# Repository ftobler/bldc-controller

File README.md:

# A bunch of BLDC controller and related PCB

Software for STM32.

PCB in Eagle.

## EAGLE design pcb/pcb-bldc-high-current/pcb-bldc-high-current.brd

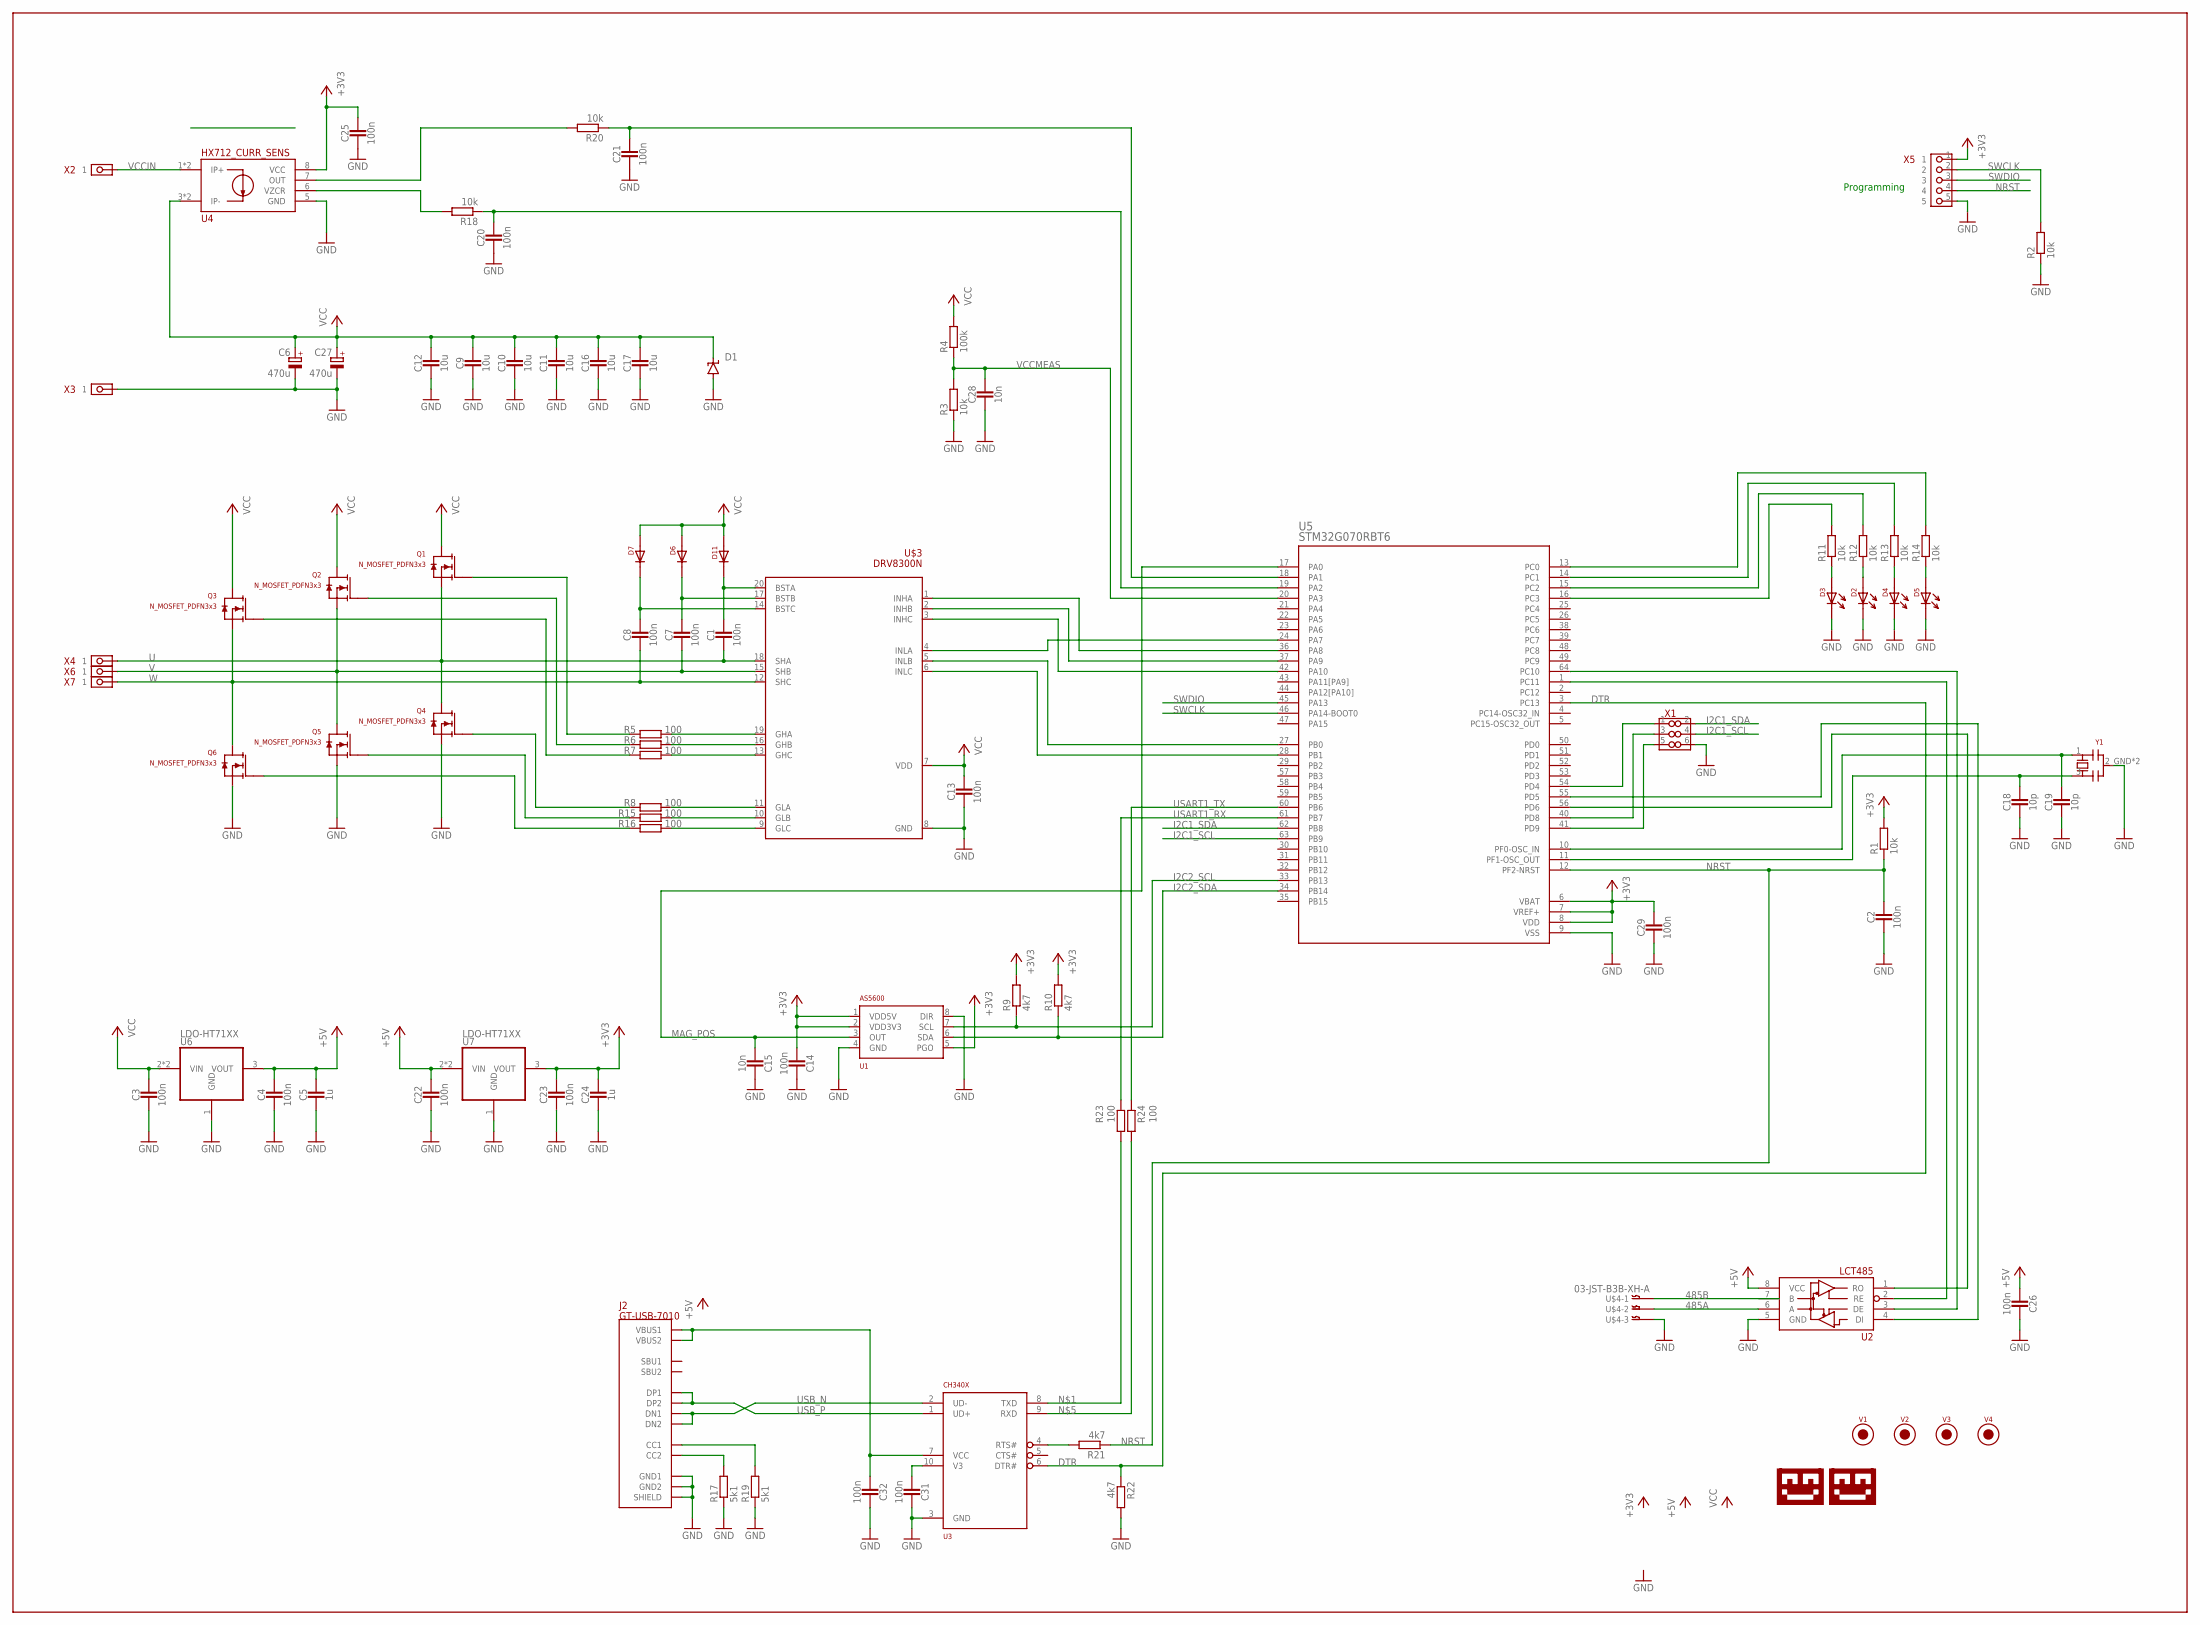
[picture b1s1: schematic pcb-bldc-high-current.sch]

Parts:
C1, C2, C3, C4, C7, C8, C13, C14, C20, C21, C22, C23, C25, C26, C29, C31, C32: 100n; 0603_CAP
C5, C24: 1u; 0603_CAP
C6, C27: 470u; 153CLV-1010
C9, C10, C11, C12, C16, C17: 10u; 1206_CAP
C15, C28: 10n; 0603_CAP
C18, C19: 10p; 0603_CAP
D1: SUPPRESSOR-SMBJ; SMBJ
D2, D3, D4, D5: LED-0805; 0805-DOT
D6, D7, D11: DIODESOD123; SOD123
J2: GT-USB-7010
Q1, Q2, Q3, Q4, Q5, Q6: N_MOSFET_PDFN3x3; DFN3X3-8L
R1, R2, R3, R11, R12, R13, R14, R18, R20: 10k; 0603-RES
R4: 100k; 0603-RES
R5, R6, R7, R8, R15, R16, R23, R24: 100; 0603-RES
R9, R10, R21, R22: 4k7; 0603-RES
R17, R19: 5k1; 0603-RES
U1: AS5600; SOIC-8
U2: LCT485_BUS_TRANSCEIVER; SOIC-8
U3: CH340X; MSOP-10
U4: HX712_CURR_SENS; SOIC-8
U5: STM32G070RBT6; LQFP-64
U6, U7: LDO-HT71XX; SOT-89
U$1: LOGO-TOBENG-1MM-FINISH; TOBENG-1MM-FINISH
U$2: LOGO-0.25MM
U$3: DRV8300N; TSSOP20
U$4: 03-JST-B3B-XH-A; B3B-XH
V1, V2, V3, V4: FIDUCIAL2MM; FIDUCIAL_2MM
X1: PIN_3X2HD; PIN_3X2_HD
X2, X3: PIN_1X1WELDINGTERMINAL; XFCNTS34031
X4, X6, X7: PIN_1X1WIRE1; PIN_1X1_SOLDERWIRE_1
X5: PIN_5X1HD; PIN_5X1_HD
Y1: 3213-QUARZ3225; 3225-QUARZ

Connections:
485A: U2.6 (A), U$4.P$2
485B: U2.7 (B), U$4.P$1
+3V3: C14.1, C23.1, C24.1, C25.1, C29.1, R1.2, R9.2, R10.2, U1.1 (VDD5V), U1.2 (VDD3V3), U1.5 (PGO), U4.8 (VCC), U5.6 (VBAT), U5.7 (VREF+), U5.8 (VDD), U7.3 (VOUT), X5.1
+5V: C4.1, C5.1, C22.1, C26.1, U2.8 (VCC), U6.3 (VOUT), U7.2 (VIN), U7.2@1 (VIN)
DTR: R22.1, U3.6 (DTR#), U5.3 (PC13)
GND: C2.2, C3.2, C4.2, C5.2, C6.-, C9.2, C10.2, C11.2, C12.2, C13.2, C14.2, C15.2, C16.2, C17.2, C18.2, C19.2, C20.2, C21.2, C22.2, C23.2, C24.2, C25.2, C26.2, C27.-, C28.2, C29.2, C31.2, C32.2, D1.A, D2.2, D3.2, D4.2, D5.2, J2.13 (SHIELD), J2.14 (SHIELD), J2.15 (SHIELD), J2.16 (SHIELD), J2.A1B12 (GND1), J2.B1A12 (GND2), J2.PAD1 (SHIELD), J2.PAD2 (SHIELD), J2.PAD3 (SHIELD), J2.PAD4 (SHIELD), J2.PAD5 (SHIELD), J2.PAD6 (SHIELD), Q4.S1 (S), Q4.S2 (S), Q4.S3 (S), Q5.S1 (S), Q5.S2 (S), Q5.S3 (S), Q6.S1 (S), Q6.S2 (S), Q6.S3 (S), R2.1, R3.1, R17.1, R19.1, R22.2, U1.4 (GND), U1.8 (DIR), U2.5 (GND), U3.3 (GND), U4.5 (GND), U5.9 (VSS), U6.1 (GND), U7.1 (GND), U$3.8 (GND), U$4.P$3, X1.6, X3.1, X3.2, X3.3, X3.4, X5.5, Y1.2_GND (2), Y1.4_GND (2)
I2C1_SCL: U5.63 (PB9), X1.4
I2C1_SDA: U5.62 (PB8), X1.2
I2C2_SCL: R9.1, U1.7 (SCL), U5.33 (PB13)
I2C2_SDA: R10.1, U1.6 (SDA), U5.34 (PB14)
MAG_POS: C15.1, U1.3 (OUT), U5.17 (PA0)
unnamed: R23.2, U3.8 (TXD)
unnamed: C18.1, U5.11 (PF1-OSC_OUT), Y1.3
unnamed: C19.1, U5.10 (PF0-OSC_IN), Y1.1
unnamed: C1.1, D11.C (2), U$3.20 (BSTA)
unnamed: R24.2, U3.9 (RXD)
unnamed: C7.1, D6.C (2), U$3.17 (BSTB)
unnamed: C8.1, D7.C (2), U$3.14 (BSTC)
unnamed: D3.1, R11.1
unnamed: U5.41 (PD9), X1.5
unnamed: Q4.G, R8.2
unnamed: Q5.G, R15.2
unnamed: Q6.G, R16.2
unnamed: Q1.G, R5.2
unnamed: Q2.G, R6.2
unnamed: Q3.G, R7.2
unnamed: D2.1, R12.1
unnamed: D4.1, R13.1
unnamed: D5.1, R14.1
unnamed: R14.2, U5.13 (PC0)
unnamed: R13.2, U5.14 (PC1)
unnamed: R12.2, U5.15 (PC2)
unnamed: R11.2, U5.16 (PC3)
unnamed: U5.36 (PA8), U$3.1 (INHA)
unnamed: U5.24 (PA7), U$3.4 (INLA)
unnamed: U5.37 (PA9), U$3.2 (INHB)
unnamed: U5.27 (PB0), U$3.5 (INLB)
unnamed: U5.42 (PA10), U$3.3 (INHC)
unnamed: U5.28 (PB1), U$3.6 (INLC)
unnamed: R5.1, U$3.19 (GHA)
unnamed: R6.1, U$3.16 (GHB)
unnamed: R7.1, U$3.13 (GHC)
unnamed: R8.1, U$3.11 (GLA)
unnamed: R15.1, U$3.10 (GLB)
unnamed: R16.1, U$3.9 (GLC)
unnamed: C32.1, J2.A4B9 (VBUS1), J2.B4A9 (VBUS2), U3.7 (VCC)
unnamed: R21.2, U3.4 (RTS#)
unnamed: U5.40 (PD8), X1.3
unnamed: C20.1, R18.1, U5.19 (PA2)
unnamed: C21.1, R20.1, U5.18 (PA1)
unnamed: R18.2, U4.6 (VZCR)
unnamed: R20.2, U4.7 (OUT)
unnamed: U2.1 (RO), U5.56 (PD6)
unnamed: U2.2 (RE), U5.1 (PC11)
unnamed: U2.3 (DE), U5.64 (PC10)
unnamed: U2.4 (DI), U5.55 (PD5)
unnamed: U5.54 (PD4), X1.1
unnamed: J2.B5 (CC2), R17.2
unnamed: J2.A5 (CC1), R19.2
unnamed: C31.1, U3.10 (V3)
NRST: C2.1, R1.1, R21.1, U5.12 (PF2-NRST), X5.4
SWCLK: R2.2, U5.46 (PA14-BOOT0), X5.2
SWDIO: U5.45 (PA13), X5.3
U: C1.2, Q1.S1 (S), Q1.S2 (S), Q1.S3 (S), Q4.D, U$3.18 (SHA), X4.P$1, X4.P$2, X4.P$3, X4.P$4, X4.P$5, X4.P$6, X4.P$7, X4.P$8, X4.P$9, X4.P$10, X4.P$11, X4.P$12, X4.P$13, X4.P$14, X4.P$15, X4.P$16, X4.P$17, X4.P$18, X4.P$19, X4.P$20
USART1_RX: R23.1, U5.61 (PB7)
USART1_TX: R24.1, U5.60 (PB6)
USB_N: J2.A7 (DN1), J2.B7 (DN2), U3.2 (UD-)
USB_P: J2.A6 (DP1), J2.B6 (DP2), U3.1 (UD+)
V: C7.2, Q2.S1 (S), Q2.S2 (S), Q2.S3 (S), Q5.D, U$3.15 (SHB), X6.P$1, X6.P$2, X6.P$3, X6.P$4, X6.P$5, X6.P$6, X6.P$7, X6.P$8, X6.P$9, X6.P$10, X6.P$11, X6.P$12, X6.P$13, X6.P$14, X6.P$15, X6.P$16, X6.P$17, X6.P$18, X6.P$19, X6.P$20
VCC: C3.1, C6.+, C9.1, C10.1, C11.1, C12.1, C13.1, C16.1, C17.1, C27.+, D1.C, D6.A (1), D7.A (1), D11.A (1), Q1.D, Q2.D, Q3.D, R4.2, U4.3 (IP-), U4.4 (IP-), U6.2 (VIN), U6.2@1 (VIN), U$3.7 (VDD)
VCCIN: U4.1 (IP+), U4.2 (IP+), X2.1, X2.2, X2.3, X2.4
VCCMEAS: C28.1, R3.2, R4.1, U5.20 (PA3)
W: C8.2, Q3.S1 (S), Q3.S2 (S), Q3.S3 (S), Q6.D, U$3.12 (SHC), X7.P$1, X7.P$2, X7.P$3, X7.P$4, X7.P$5, X7.P$6, X7.P$7, X7.P$8, X7.P$9, X7.P$10, X7.P$11, X7.P$12, X7.P$13, X7.P$14, X7.P$15, X7.P$16, X7.P$17, X7.P$18, X7.P$19, X7.P$20

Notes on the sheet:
Programming

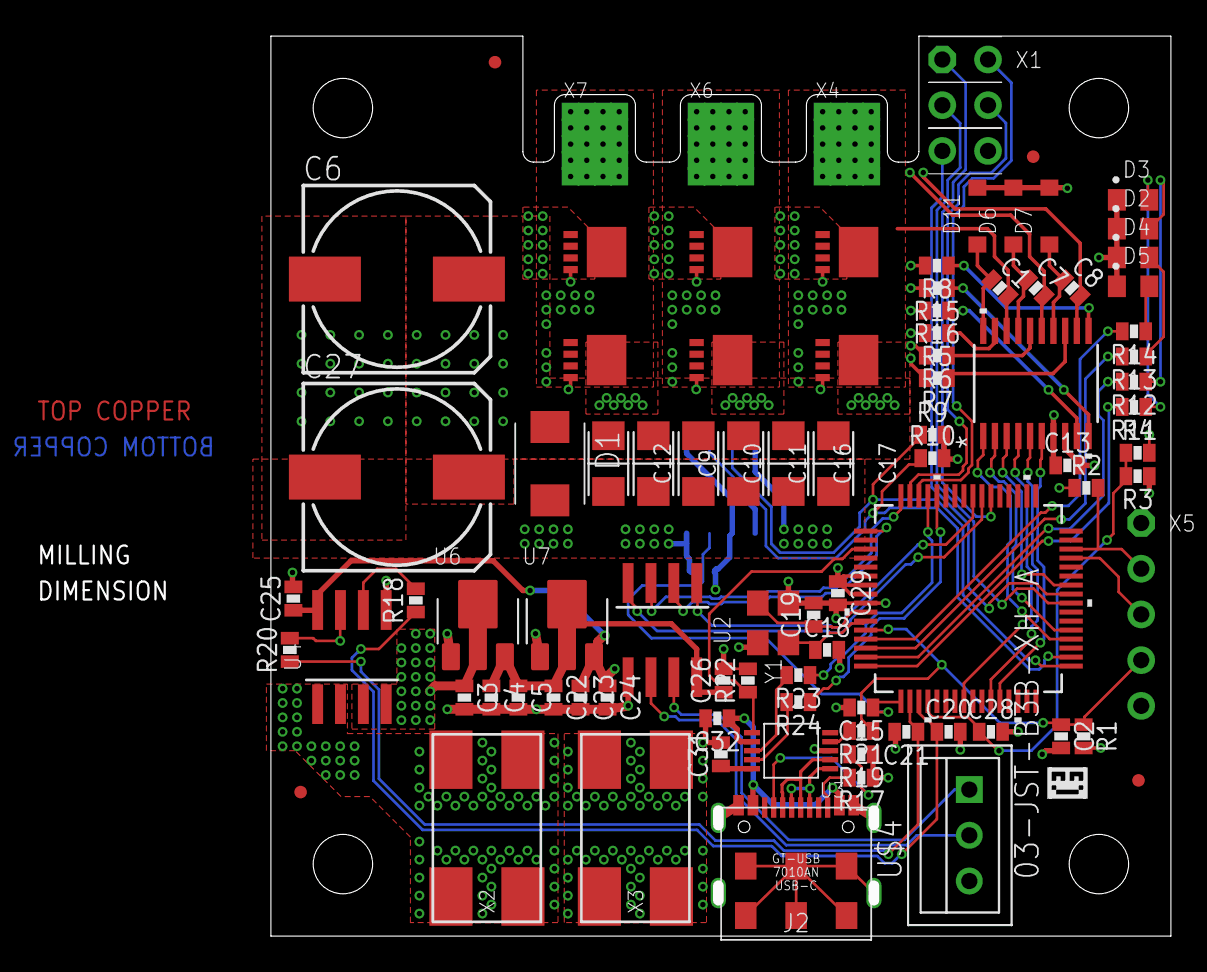
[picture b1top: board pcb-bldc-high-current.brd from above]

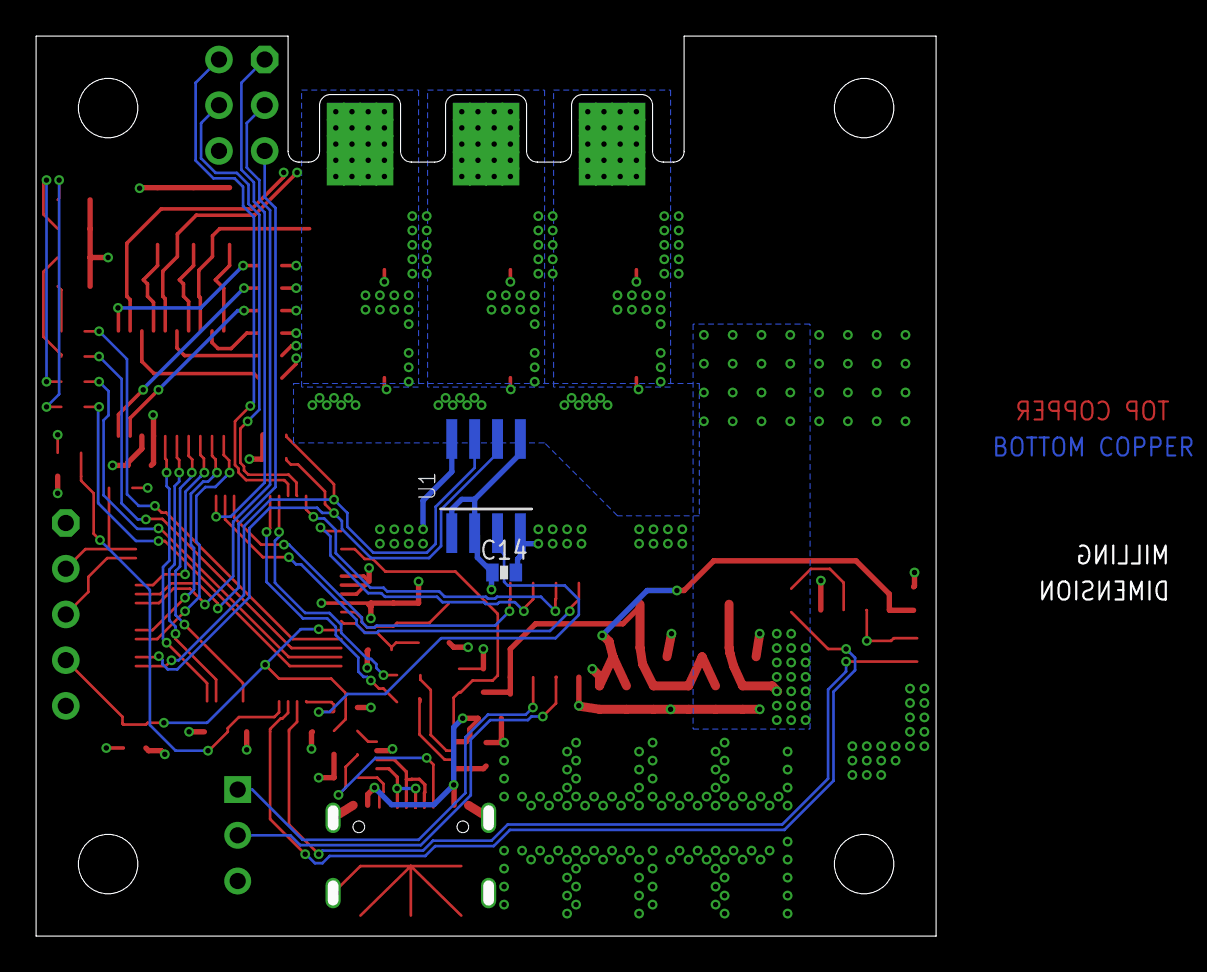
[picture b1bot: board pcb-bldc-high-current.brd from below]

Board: 4 copper layers, 50.0 x 50.0 mm, 93 parts (3 on the bottom side), 73 nets.

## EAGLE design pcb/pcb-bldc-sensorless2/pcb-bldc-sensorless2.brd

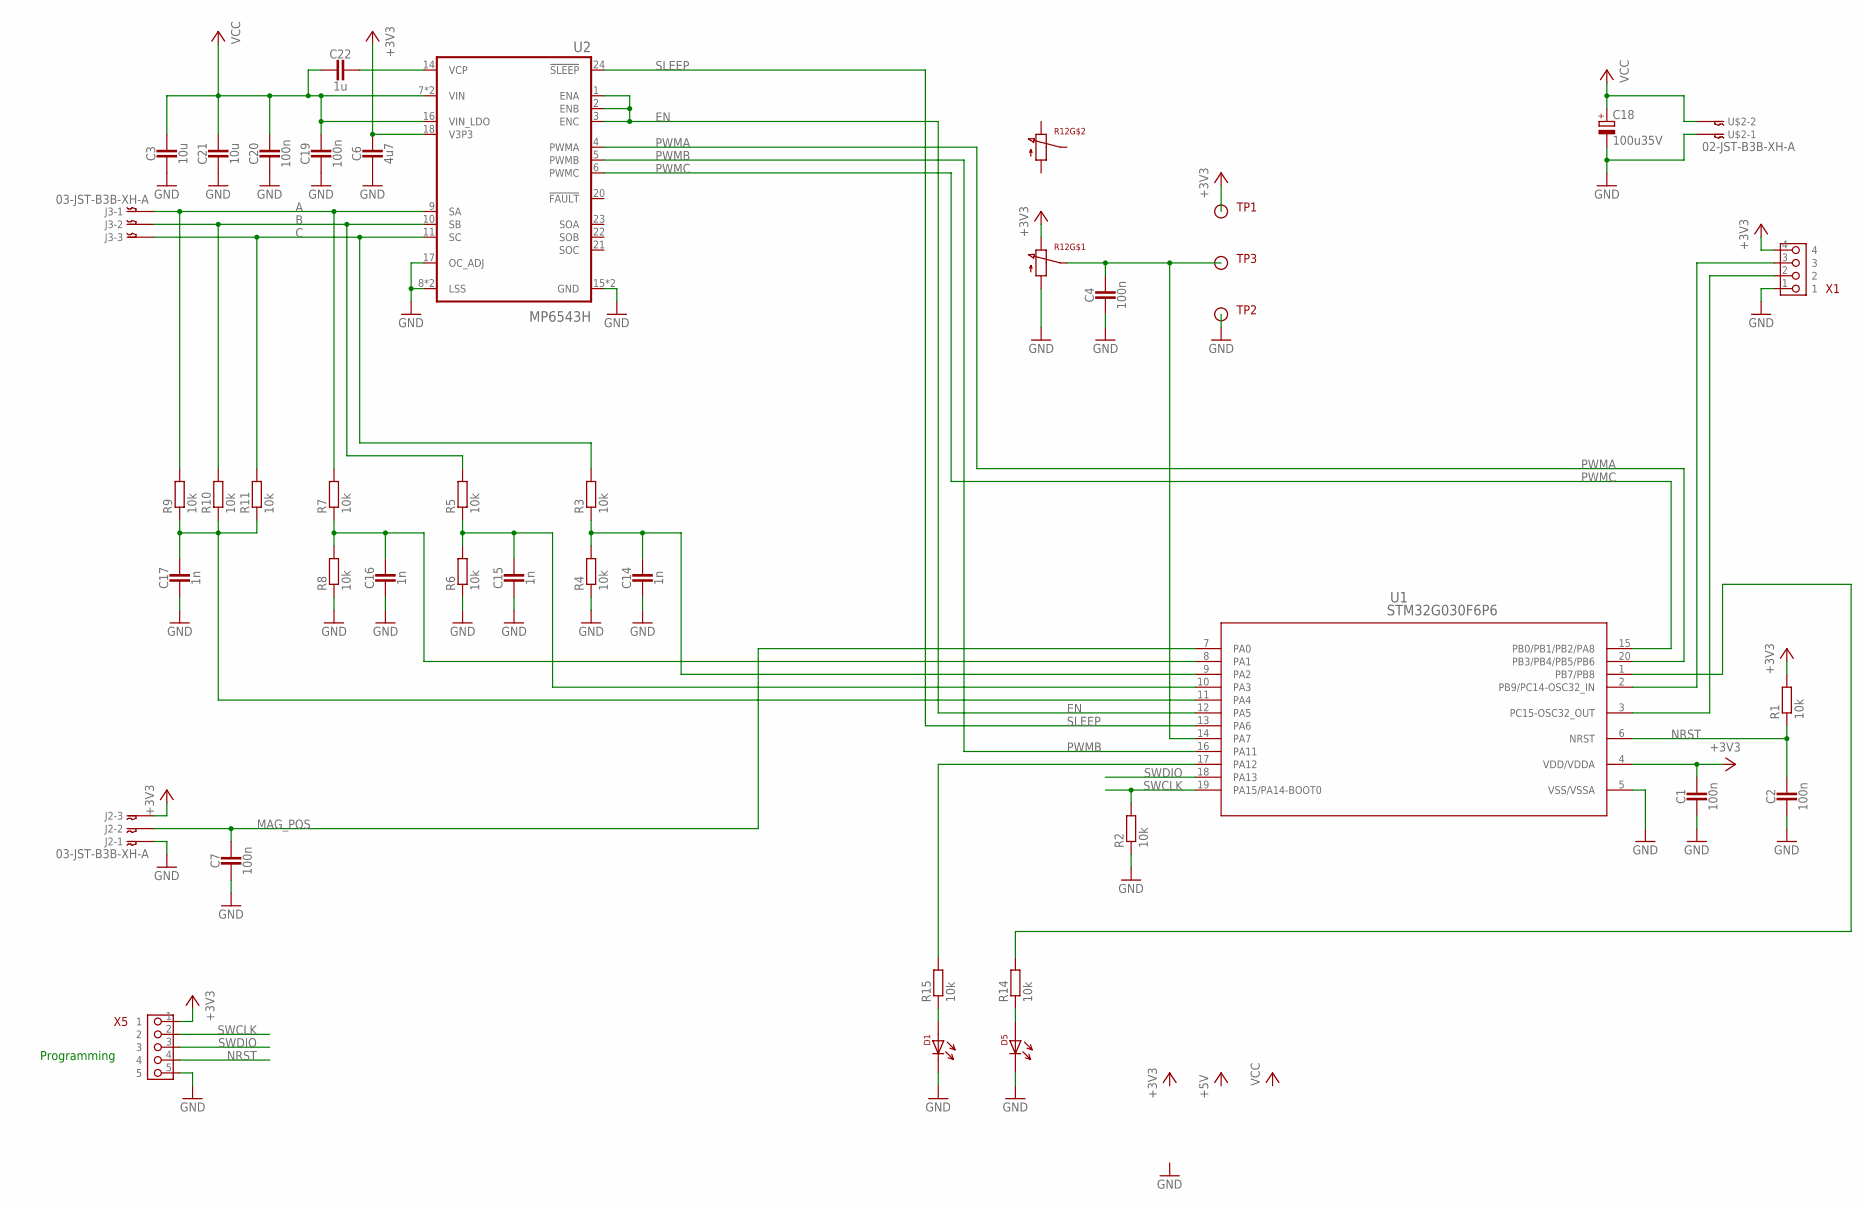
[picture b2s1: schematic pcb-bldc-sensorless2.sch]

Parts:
C1, C2, C4, C7, C19, C20: 100n; 0603_CAP
C3, C21: 10u; 1206_CAP
C6: 4u7; 0805_CAP
C14, C15, C16, C17: 1n; 0603_CAP
C18: 100u35V; 153CLV-0605
C22: 1u; 0603_CAP
D1, D5: LED-0805; 0805-DOT
J2, J3: 03-JST-B3B-XH-A; B3B-XH
R1, R2, R3, R4, R5, R6, R7, R8, R9, R10, R11, R14, R15: 10k; 0603-RES
R12: POTDUAL; ALPS_RK097
TP1, TP2, TP3: TESTPIN; PIN-SMD-1X1-TEST_1M5
U1: STM32G030F6P6; TSSOP20
U2: MP6543H; QFN24
U$2: 02-JST-B3B-XH-A; B2B-XH
X1: PIN_4X1HD; PIN_4X1_HD
X5: PIN_5X1HD; PIN_5X1_HD

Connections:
+3V3: C1.1, C6.P$1 (1), J2.P$3, R1.2, R12.R11 (1), TP1.1, U1.4 (VDD/VDDA), U2.18 (V3P3), X1.4, X5.1
A: J3.P$1, R7.2, R9.2, U2.9 (SA)
B: J3.P$2, R5.2, R10.2, U2.10 (SB)
C: J3.P$3, R3.2, R11.2, U2.11 (SC)
EN: U1.12 (PA5), U2.1 (ENA), U2.2 (ENB), U2.3 (ENC)
GND: C1.2, C2.2, C3.2, C4.2, C6.P$2 (2), C7.2, C14.2, C15.2, C16.2, C17.2, C18.-, C19.2, C20.2, C21.2, D1.2, D5.2, J2.P$1, R2.1, R4.1, R6.1, R8.1, R12.R13 (3), TP2.1, U1.5 (VSS/VSSA), U2.8 (LSS), U2.12 (LSS), U2.15 (GND), U2.17 (OC_ADJ), U2.25 (GND), U$2.P$1, X1.1, X5.5
MAG_POS: C7.1, J2.P$2, U1.7 (PA0)
unnamed: C4.1, R12.R12 (2), TP3.1, U1.14 (PA7)
unnamed: C14.1, R3.1, R4.2, U1.9 (PA2)
unnamed: C15.1, R5.1, R6.2, U1.10 (PA3)
unnamed: C17.1, R9.1, R10.1, R11.1, U1.11 (PA4)
unnamed: U1.3 (PC15-OSC32_OUT), X1.2
unnamed: D1.1, R15.1
unnamed: C16.1, R7.1, R8.2, U1.8 (PA1)
unnamed: R15.2, U1.17 (PA12)
unnamed: R14.2, U1.1 (PB7/PB8)
unnamed: D5.1, R14.1
unnamed: U1.2 (PB9/PC14-OSC32_IN), X1.3
unnamed: C22.1, U2.14 (VCP)
NRST: C2.1, R1.1, U1.6 (NRST), X5.4
PWMA: U1.20 (PB3/PB4/PB5/PB6), U2.4 (PWMA)
PWMB: U1.16 (PA11), U2.5 (PWMB)
PWMC: U1.15 (PB0/PB1/PB2/PA8), U2.6 (PWMC)
SLEEP: U1.13 (PA6), U2.24 (!SLEEP)
SWCLK: R2.2, U1.19 (PA15/PA14-BOOT0), X5.2
SWDIO: U1.18 (PA13), X5.3
VCC: C3.1, C18.+, C19.1, C20.1, C21.1, C22.2, U2.7 (VIN), U2.13 (VIN), U2.16 (VIN_LDO), U$2.P$2

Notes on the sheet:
Programming

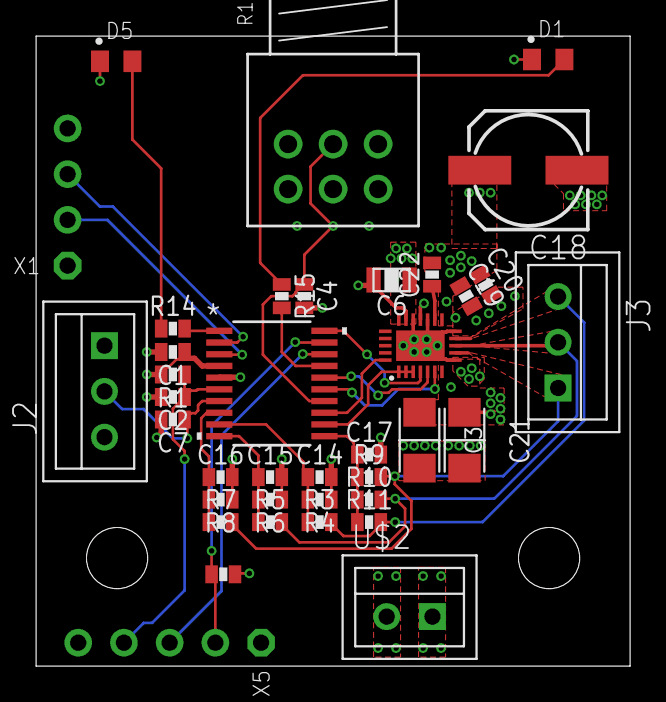
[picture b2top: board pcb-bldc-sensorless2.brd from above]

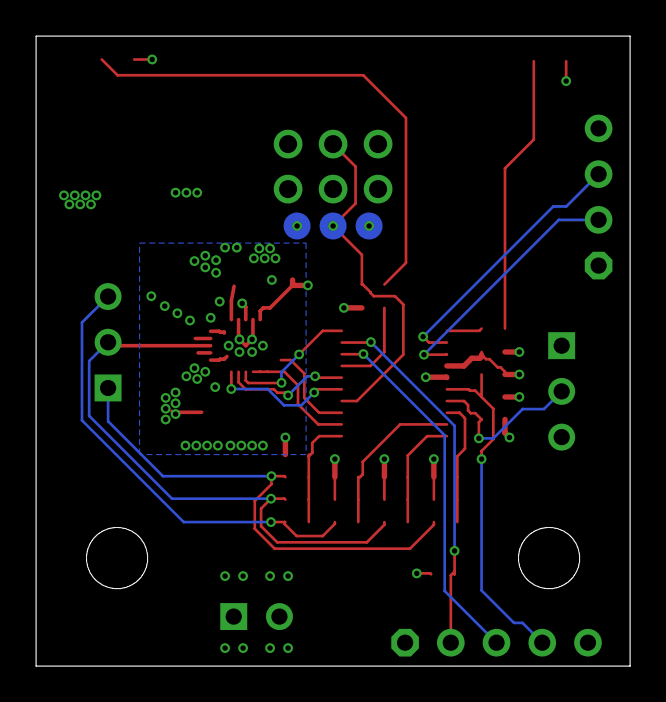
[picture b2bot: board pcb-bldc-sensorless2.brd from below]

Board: 4 copper layers, 33.0 x 35.0 mm, 41 parts (3 on the bottom side), 27 nets.

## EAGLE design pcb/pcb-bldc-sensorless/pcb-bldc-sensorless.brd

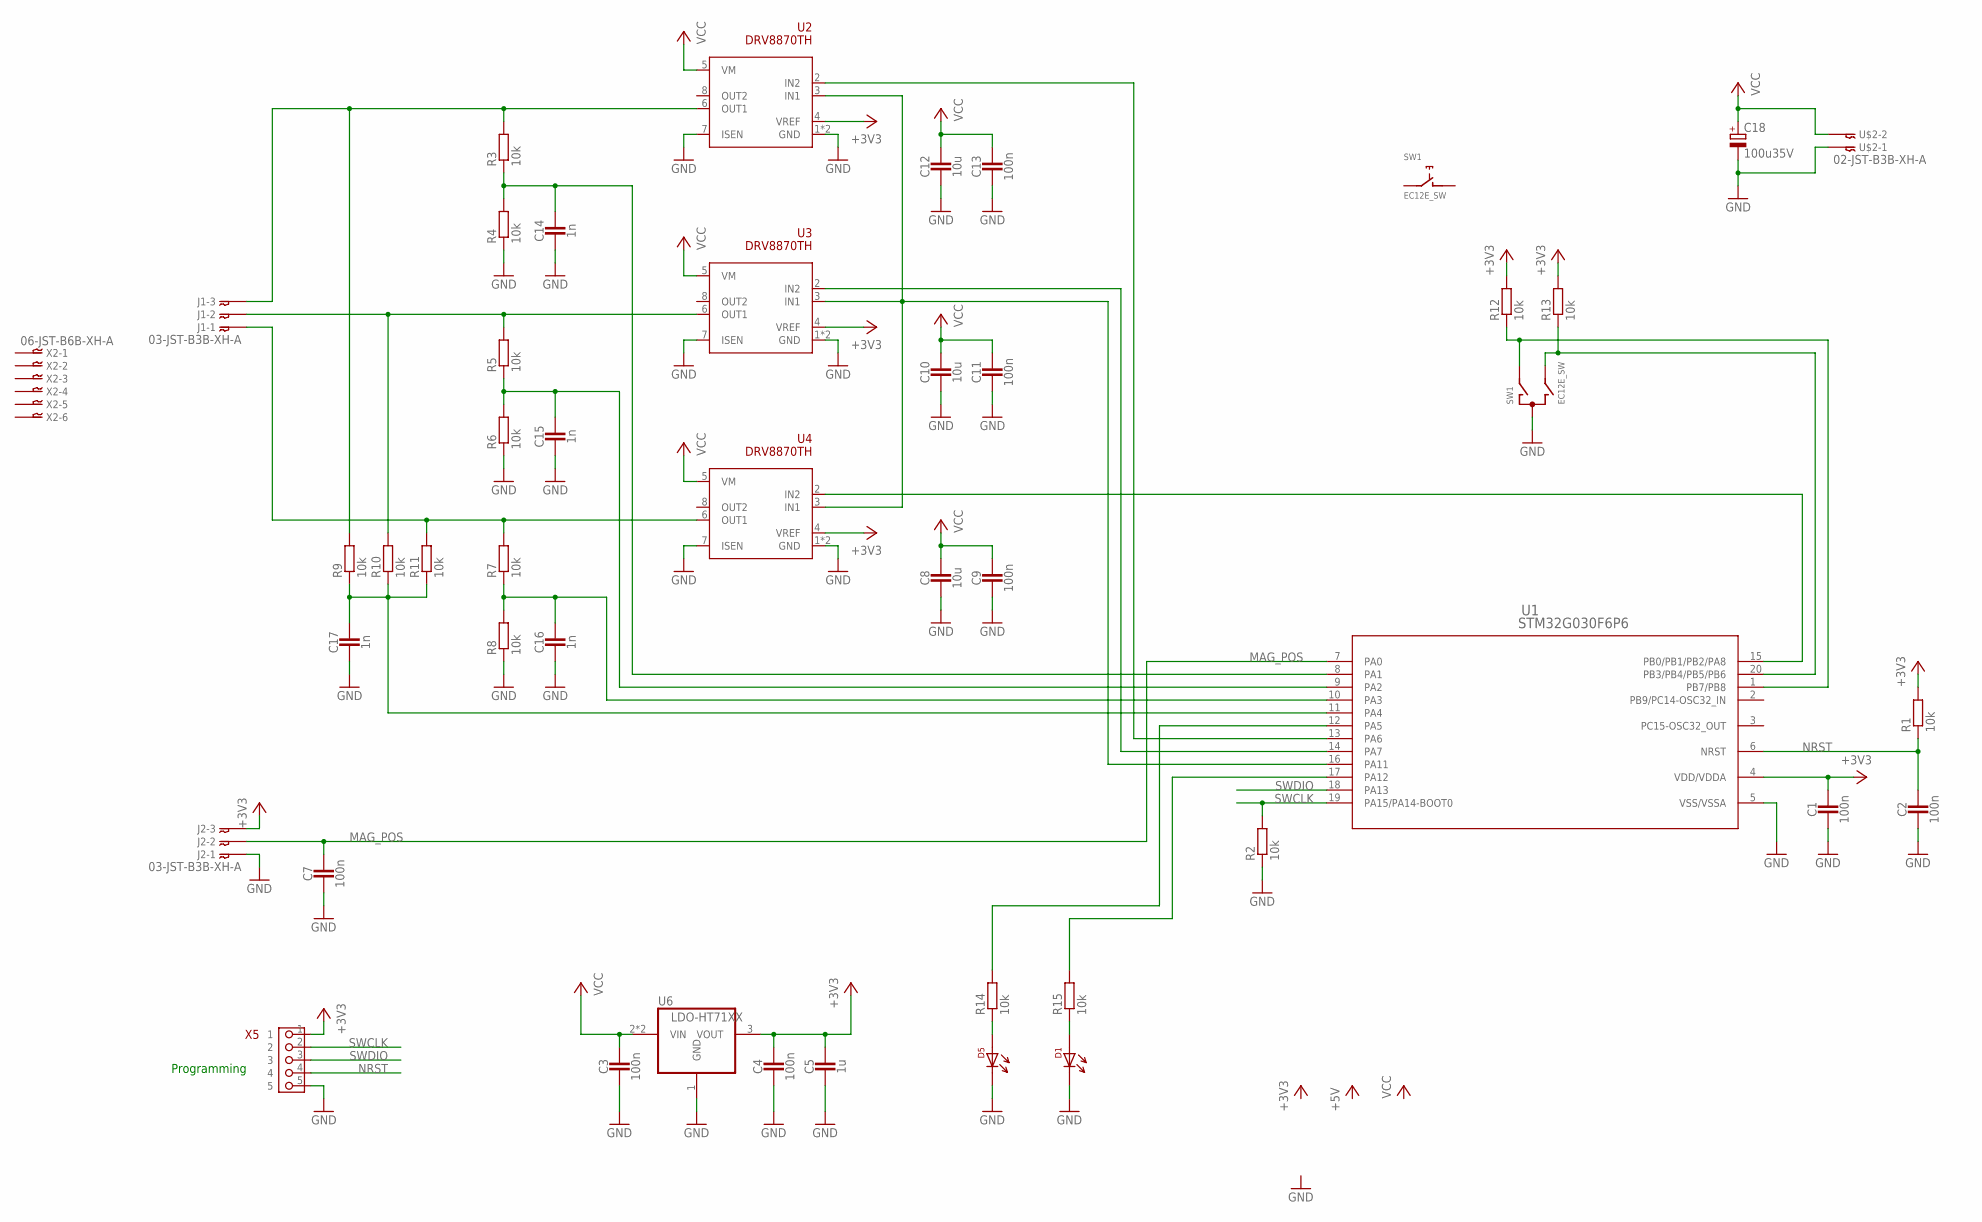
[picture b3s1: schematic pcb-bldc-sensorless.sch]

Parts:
C1, C2, C3, C4, C7, C9, C11, C13: 100n; 0603_CAP
C5: 1u; 0603_CAP
C8, C10, C12: 10u; 1206_CAP
C14, C15, C16, C17: 1n; 0603_CAP
C18: 100u35V; 153CLV-0605
D1, D5: LED-0805; 0805-DOT
J1, J2: 03-JST-B3B-XH-A; B3B-XH
R1, R2, R3, R4, R5, R6, R7, R8, R9, R10, R11, R12, R13, R14, R15: 10k; 0603-RES
SW1: EC12E_SW; ALPS_EC12E_SW
U1: STM32G030F6P6; TSSOP20
U2, U3, U4: DRV8870TH; SOIC-8-THERM
U6: LDO-HT71XX; SOT-89
U$2: 02-JST-B3B-XH-A; B2B-XH
X2: 06-JST-B6B-XH-A; B6B-XH
X5: PIN_5X1HD; PIN_5X1_HD

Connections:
+3V3: C1.1, C4.1, C5.1, J2.P$3, R1.2, R12.2, R13.2, U1.4 (VDD/VDDA), U2.4 (VREF), U3.4 (VREF), U4.4 (VREF), U6.3 (VOUT), X5.1
GND: C1.2, C2.2, C3.2, C4.2, C5.2, C7.2, C8.2, C9.2, C10.2, C11.2, C12.2, C13.2, C14.2, C15.2, C16.2, C17.2, C18.-, D1.2, D5.2, J2.P$1, R2.1, R4.1, R6.1, R8.1, SW1.C, U1.5 (VSS/VSSA), U2.1 (GND), U2.7 (ISEN), U2.9 (GND), U3.1 (GND), U3.7 (ISEN), U3.9 (GND), U4.1 (GND), U4.7 (ISEN), U4.9 (GND), U6.1 (GND), U$2.P$1, X5.5
MAG_POS: C7.1, J2.P$2, U1.7 (PA0)
unnamed: U1.16 (PA11), U2.3 (IN1), U3.3 (IN1), U4.3 (IN1)
unnamed: C14.1, R3.1, R4.2, U1.8 (PA1)
unnamed: J1.P$2, R5.2, R10.2, U3.6 (OUT1)
unnamed: J1.P$3, R3.2, R9.2, U2.6 (OUT1)
unnamed: U1.13 (PA6), U2.2 (IN2)
unnamed: U1.14 (PA7), U3.2 (IN2)
unnamed: J1.P$1, R7.2, R11.2, U4.6 (OUT1)
unnamed: C15.1, R5.1, R6.2, U1.9 (PA2)
unnamed: U1.15 (PB0/PB1/PB2/PA8), U4.2 (IN2)
unnamed: C16.1, R7.1, R8.2, U1.10 (PA3)
unnamed: C17.1, R9.1, R10.1, R11.1, U1.11 (PA4)
unnamed: R12.1, SW1.A, U1.1 (PB7/PB8)
unnamed: R13.1, SW1.B, U1.20 (PB3/PB4/PB5/PB6)
unnamed: D1.1, R15.1
unnamed: R14.2, U1.12 (PA5)
unnamed: R15.2, U1.17 (PA12)
unnamed: D5.1, R14.1
NRST: C2.1, R1.1, U1.6 (NRST), X5.4
SWCLK: R2.2, U1.19 (PA15/PA14-BOOT0), X5.2
SWDIO: U1.18 (PA13), X5.3
VCC: C3.1, C8.1, C9.1, C10.1, C11.1, C12.1, C13.1, C18.+, U2.5 (VM), U3.5 (VM), U4.5 (VM), U6.2 (VIN), U6.2@1 (VIN), U$2.P$2

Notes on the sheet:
Programming

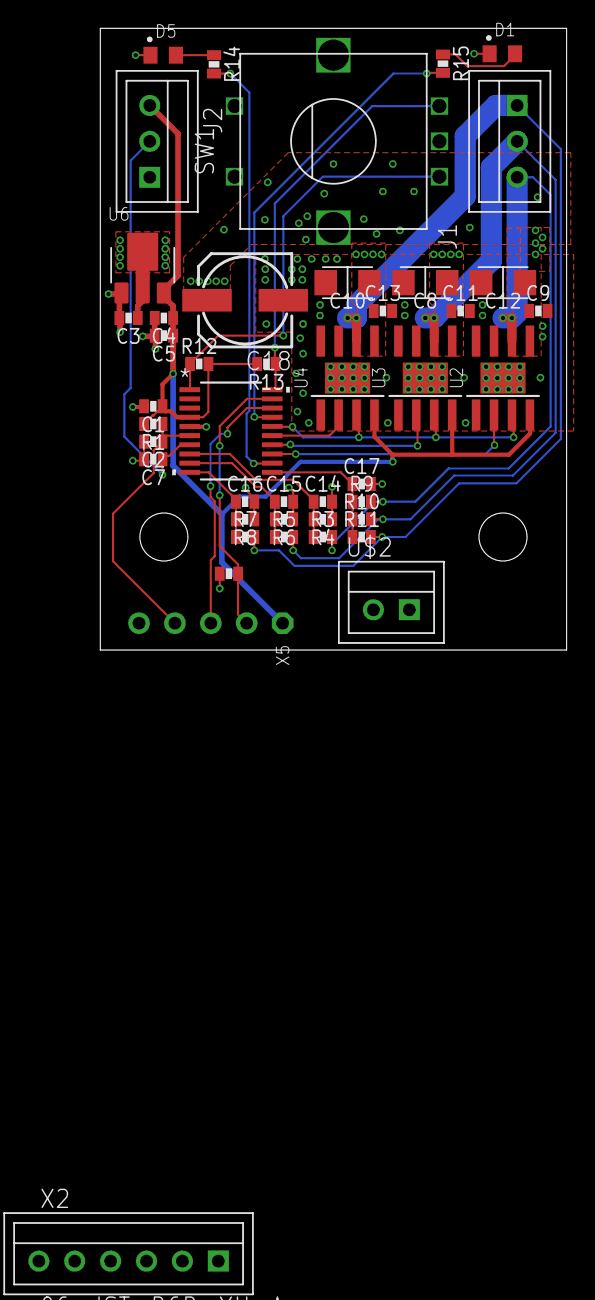
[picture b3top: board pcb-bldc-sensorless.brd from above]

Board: 4 copper layers, 33.0 x 44.0 mm, 45 parts (0 on the bottom side), 24 nets.

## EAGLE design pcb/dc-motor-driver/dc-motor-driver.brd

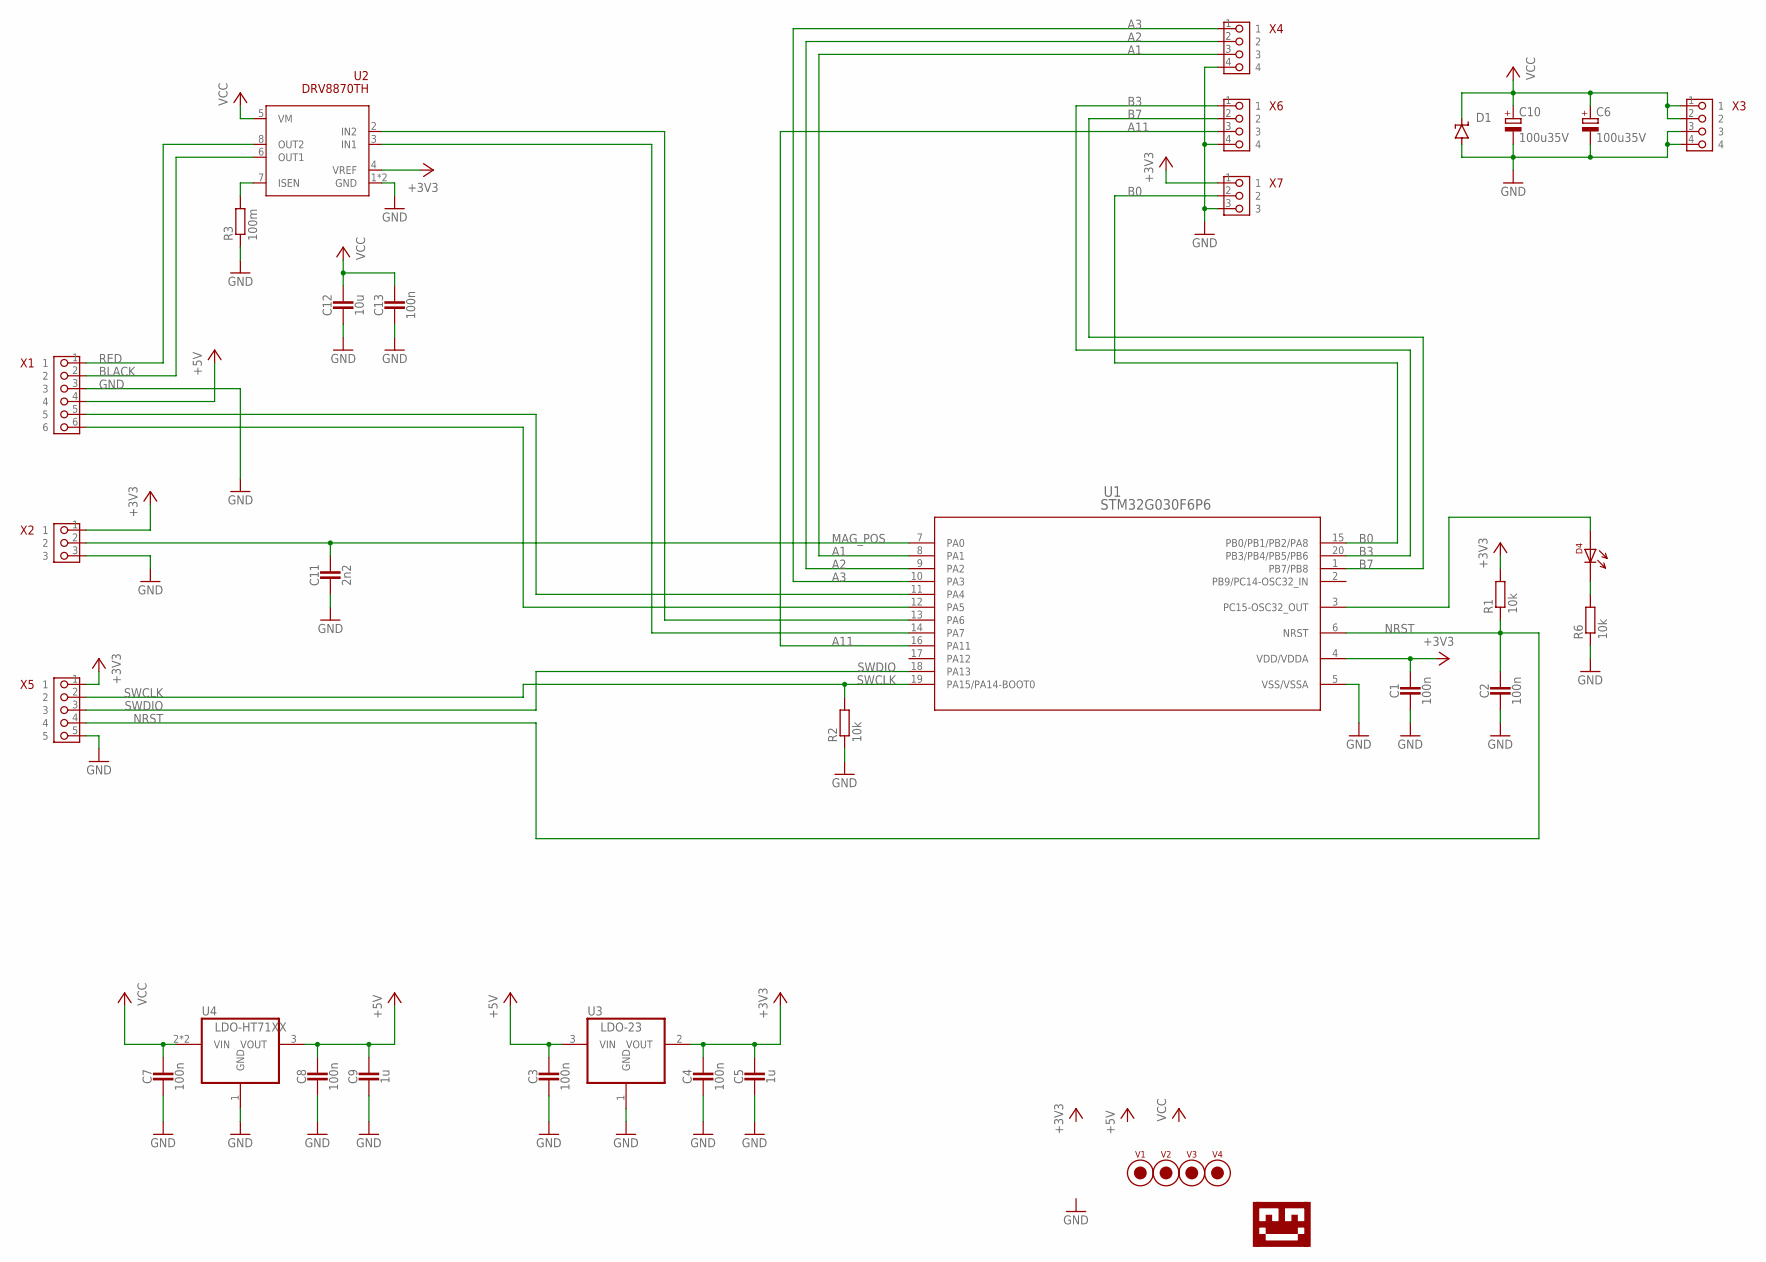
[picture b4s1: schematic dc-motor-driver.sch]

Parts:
C1, C2, C3, C4, C7, C8, C13: 100n; 0603_CAP
C5, C9: 1u; 0603_CAP
C6, C10: 100u35V; 153CLV-0605
C11: 2n2; 0603_CAP
C12: 10u; 1206_CAP
D1: SUPPRESSOR-SMBJ; SMBJ
D4: LED-0805; 0805-DOT
R1, R2, R6: 10k; 0603-RES
R3: 100m; 1206_RES_HIGH_CLEARANCE
U1: STM32G030F6P6; TSSOP20
U2: DRV8870TH; SOIC-8-THERM
U3: LDO-23; SOT-23
U4: LDO-HT71XX; SOT-89
U$1: LOGO-TOBENG-4MM-FINISH; TOBENG-4MM-FINISH
V1, V2, V3, V4: FIDUCIAL2MM; FIDUCIAL_2MM
X1: PIN_6X1HD; PIN_6X1_HD
X2, X7: PIN_3X1HD; PIN_3X1_HD
X3, X4, X6: PIN_4X1HD; PIN_4X1_HD
X5: PIN_5X1HD; PIN_5X1_HD

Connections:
+3V3: C1.1, C4.1, C5.1, R1.2, U1.4 (VDD/VDDA), U2.4 (VREF), U3.2 (VOUT), X2.1, X5.1, X7.1
+5V: C3.1, C8.1, C9.1, U3.3 (VIN), U4.3 (VOUT), X1.4
A1: U1.8 (PA1), X4.3
A2: U1.9 (PA2), X4.2
A3: U1.10 (PA3), X4.1
A11: U1.16 (PA11), X6.3
B0: U1.15 (PB0/PB1/PB2/PA8), X7.2
B3: U1.20 (PB3/PB4/PB5/PB6), X6.1
B7: U1.1 (PB7/PB8), X6.2
BLACK: U2.6 (OUT1), X1.2
D5: D4.1, U1.3 (PC15-OSC32_OUT)
GND: C1.2, C2.2, C3.2, C4.2, C5.2, C6.-, C7.2, C8.2, C9.2, C10.-, C11.2, C12.2, C13.2, D1.A, R2.1, R3.1, R6.1, U1.5 (VSS/VSSA), U2.1 (GND), U2.9 (GND), U3.1 (GND), U4.1 (GND), X1.3, X2.3, X3.3, X3.4, X4.4, X5.5, X6.4, X7.3
M0U: U1.13 (PA6), U2.2 (IN2)
MAG_POS: C11.1, U1.7 (PA0), X2.2
unnamed: R3.2, U2.7 (ISEN)
unnamed: U1.14 (PA7), U2.3 (IN1)
unnamed: D4.2, R6.2
unnamed: U1.12 (PA5), X1.6
unnamed: U1.11 (PA4), X1.5
NRST: C2.1, R1.1, U1.6 (NRST), X5.4
RED: U2.8 (OUT2), X1.1
SWCLK: R2.2, U1.19 (PA15/PA14-BOOT0), X5.2
SWDIO: U1.18 (PA13), X5.3
VCC: C6.+, C7.1, C10.+, C12.1, C13.1, D1.C, U2.5 (VM), U4.2 (VIN), U4.2@1 (VIN), X3.1, X3.2

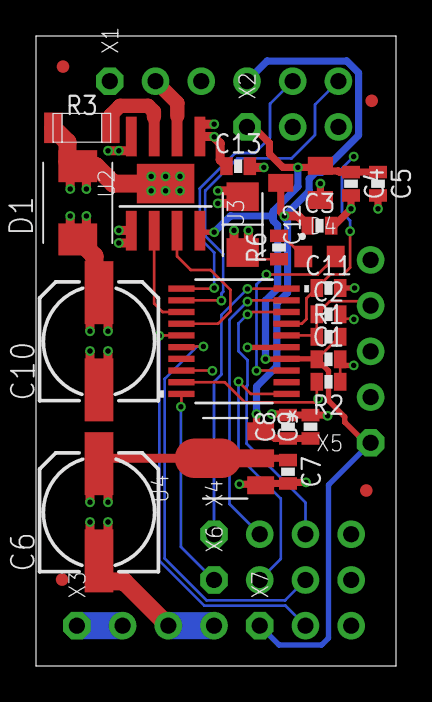
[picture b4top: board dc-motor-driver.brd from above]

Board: 4 copper layers, 20.0 x 35.0 mm, 35 parts (1 on the bottom side), 24 nets.

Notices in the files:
parts and their libraries:
COPYRIGHT: Copyright (C) 2024 Ultra Librarian. All rights reserved.
